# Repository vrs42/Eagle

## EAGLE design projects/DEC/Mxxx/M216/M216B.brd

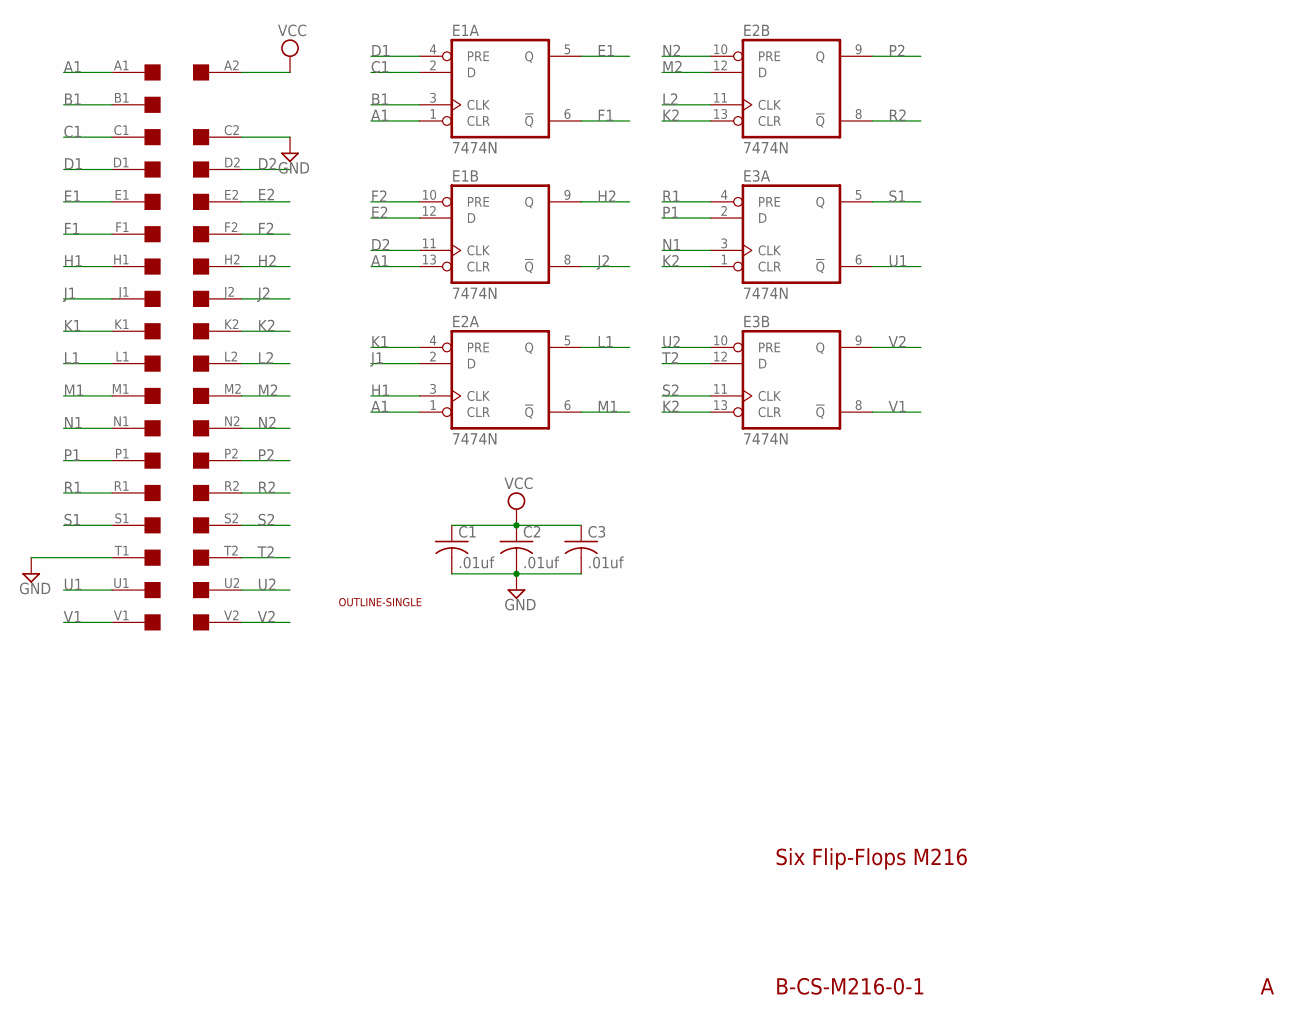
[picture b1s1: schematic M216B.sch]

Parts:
C1, C2, C3: .01uf; C050-025X075
E1, E2, E3: 7474N; DIL14
U$1: OUTLINE-SINGLE; SINGLE
U$4: SINGLE; EDGE-CON2

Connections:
A1: E1.1 (CLR), E1.13 (CLR), E2.1 (CLR), U$4.A1
B1: E1.3 (CLK), U$4.B1
C1: E1.2 (D), U$4.C1
D1: E1.4 (PRE), U$4.D1
D2: E1.11 (CLK), U$4.D2
E1: E1.5 (Q), U$4.E1
E2: E1.12 (D), U$4.E2
F1: E1.6 (!Q), U$4.F1
F2: E1.10 (PRE), U$4.F2
GND: C1.2, C2.2, C3.2, E1.7 (GND), E2.7 (GND), E3.7 (GND), U$4.C2, U$4.T1
H1: E2.3 (CLK), U$4.H1
H2: E1.9 (Q), U$4.H2
J1: E2.2 (D), U$4.J1
J2: E1.8 (!Q), U$4.J2
K1: E2.4 (PRE), U$4.K1
K2: E2.13 (CLR), E3.1 (CLR), E3.13 (CLR), U$4.K2
L1: E2.5 (Q), U$4.L1
L2: E2.11 (CLK), U$4.L2
M1: E2.6 (!Q), U$4.M1
M2: E2.12 (D), U$4.M2
N1: E3.3 (CLK), U$4.N1
N2: E2.10 (PRE), U$4.N2
P1: E3.2 (D), U$4.P1
P2: E2.9 (Q), U$4.P2
R1: E3.4 (PRE), U$4.R1
R2: E2.8 (!Q), U$4.R2
S1: E3.5 (Q), U$4.S1
S2: E3.11 (CLK), U$4.S2
T2: E3.12 (D), U$4.T2
U1: E3.6 (!Q), U$4.U1
U2: E3.10 (PRE), U$4.U2
V1: E3.8 (!Q), U$4.V1
V2: E3.9 (Q), U$4.V2
VCC: C1.1, C2.1, C3.1, E1.14 (VCC), E2.14 (VCC), E3.14 (VCC), U$4.A2

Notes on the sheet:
B-CS-M216-0-1
Six Flip-Flops M216

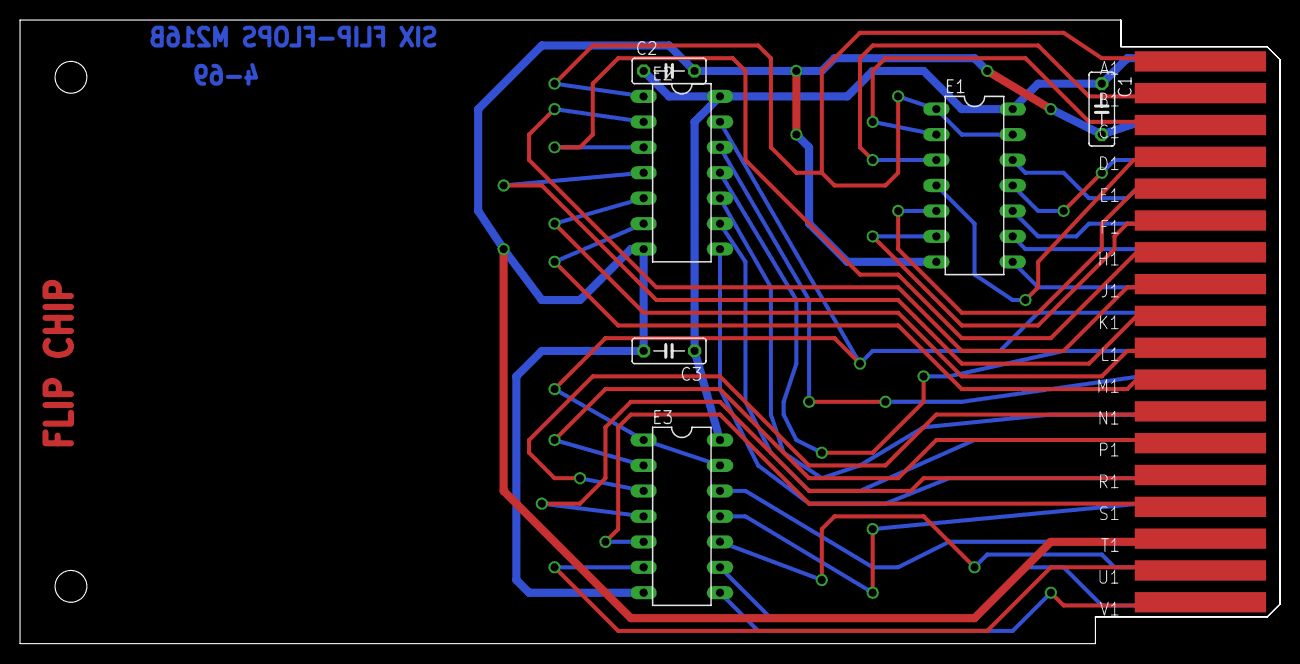
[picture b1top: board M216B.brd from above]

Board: 2 copper layers, 125.7 x 62.2 mm, 9 parts (0 on the bottom side), 34 nets.

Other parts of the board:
U$5: FLIPCHIP

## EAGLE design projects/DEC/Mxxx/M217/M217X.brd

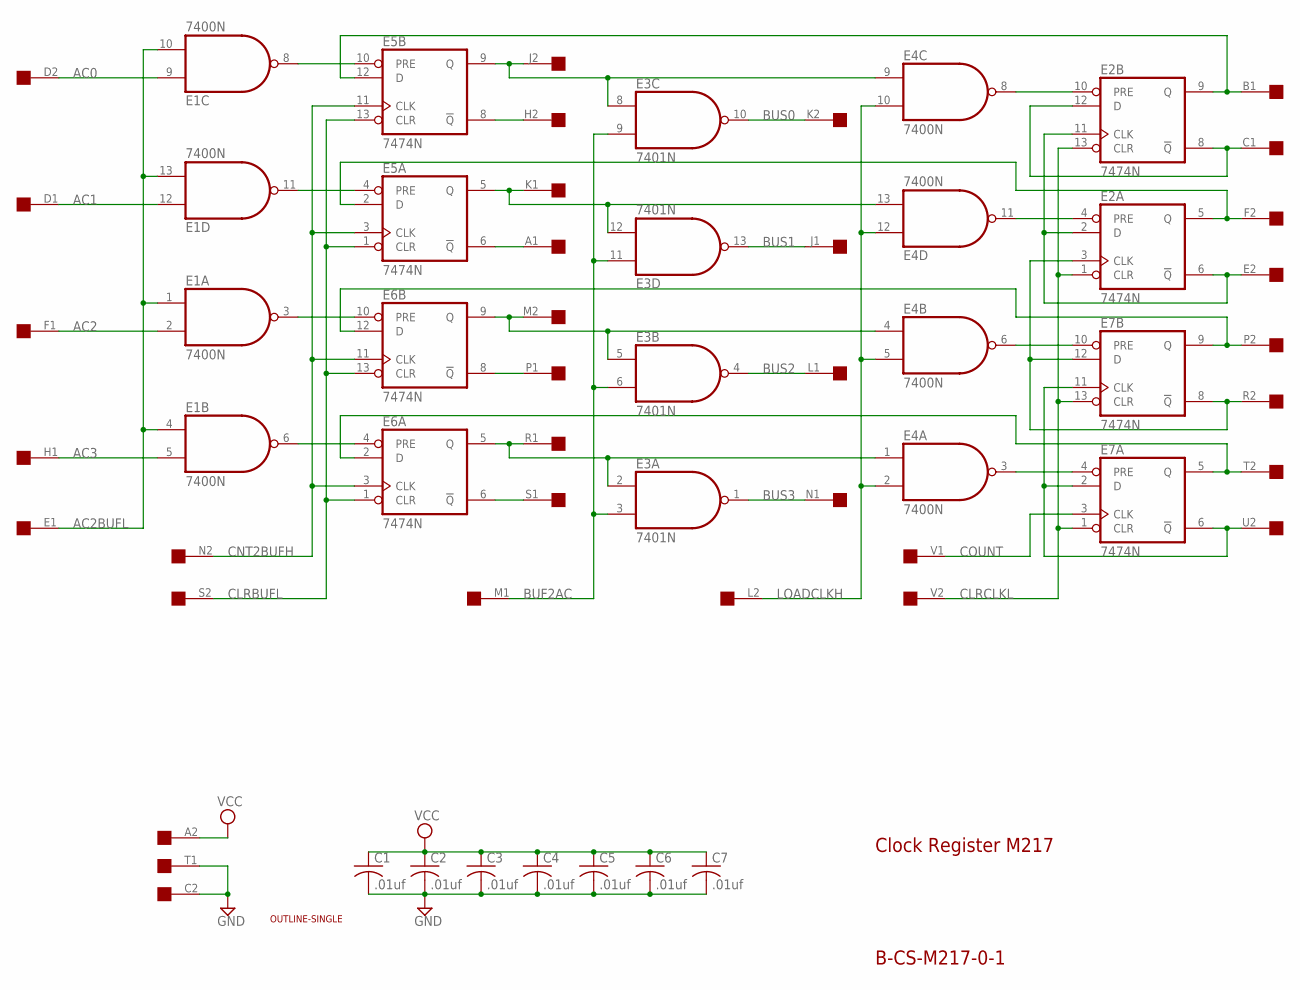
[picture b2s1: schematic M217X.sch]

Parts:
C1, C2, C3, C4, C5, C6, C7: .01uf; C050-025X075
E1, E4: 7400N; DIL14
E2, E5, E6, E7: 7474N; DIL14
E3: 7401N; DIL14
U$1: OUTLINE-SINGLE; SINGLE
U$4: SINGLE; EDGE-CON2

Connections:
AC0: E1.9 (I0), U$4.D2
AC1: E1.12 (I0), U$4.D1
AC2: E1.2 (I1), U$4.F1
AC2BUFL: E1.1 (I0), E1.4 (I0), E1.10 (I1), E1.13 (I1), U$4.E1
AC3: E1.5 (I1), U$4.H1
BUF2AC: E3.3 (I1), E3.6 (I1), E3.9 (I1), E3.11 (I0), U$4.M1
BUS0: E3.10 (O), U$4.K2
BUS1: E3.13 (O), U$4.J1
BUS2: E3.4 (O), U$4.L1
BUS3: E3.1 (O), U$4.N1
CLRBUFL: E5.1 (CLR), E5.13 (CLR), E6.1 (CLR), E6.13 (CLR), U$4.S2
CLRCLKL: E2.1 (CLR), E2.13 (CLR), E7.1 (CLR), E7.13 (CLR), U$4.V2
CNT2BUFH: E5.3 (CLK), E5.11 (CLK), E6.3 (CLK), E6.11 (CLK), U$4.N2
COUNT: E7.3 (CLK), U$4.V1
GND: C1.2, C2.2, C3.2, C4.2, C5.2, C6.2, C7.2, E1.7 (GND), E2.7 (GND), E3.7 (GND), E4.7 (GND), E5.7 (GND), E6.7 (GND), E7.7 (GND), U$4.C2, U$4.T1
LOADCLKH: E4.2 (I1), E4.5 (I1), E4.10 (I1), E4.12 (I0), U$4.L2
unnamed: E6.12 (D), E7.9 (Q), U$4.P2
unnamed: E2.5 (Q), E5.2 (D), U$4.F2
unnamed: E1.6 (O), E6.4 (PRE)
unnamed: E1.3 (O), E6.10 (PRE)
unnamed: E1.11 (O), E5.4 (PRE)
unnamed: E1.8 (O), E5.10 (PRE)
unnamed: E3.8 (I0), E4.9 (I0), E5.9 (Q), U$4.J2
unnamed: E5.8 (!Q), U$4.H2
unnamed: E3.12 (I1), E4.13 (I1), E5.5 (Q), U$4.K1
unnamed: E5.6 (!Q), U$4.A1
unnamed: E3.5 (I0), E4.4 (I0), E6.9 (Q), U$4.M2
unnamed: E6.8 (!Q), U$4.P1
unnamed: E3.2 (I0), E4.1 (I0), E6.5 (Q), U$4.R1
unnamed: E6.6 (!Q), U$4.S1
unnamed: E4.3 (O), E7.4 (PRE)
unnamed: E4.6 (O), E7.10 (PRE)
unnamed: E2.4 (PRE), E4.11 (O)
unnamed: E2.10 (PRE), E4.8 (O)
unnamed: E7.2 (D), E7.6 (!Q), E7.11 (CLK), U$4.U2
unnamed: E6.2 (D), E7.5 (Q), U$4.T2
unnamed: E2.3 (CLK), E7.8 (!Q), E7.12 (D), U$4.R2
unnamed: E2.2 (D), E2.6 (!Q), E2.11 (CLK), U$4.E2
unnamed: E2.9 (Q), E5.12 (D), U$4.B1
unnamed: E2.8 (!Q), E2.12 (D), U$4.C1
VCC: C1.1, C2.1, C3.1, C4.1, C5.1, C6.1, C7.1, E1.14 (VCC), E2.14 (VCC), E3.14 (VCC), E4.14 (VCC), E5.14 (VCC), E6.14 (VCC), E7.14 (VCC), U$4.A2

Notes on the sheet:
B-CS-M217-0-1
Clock Register M217

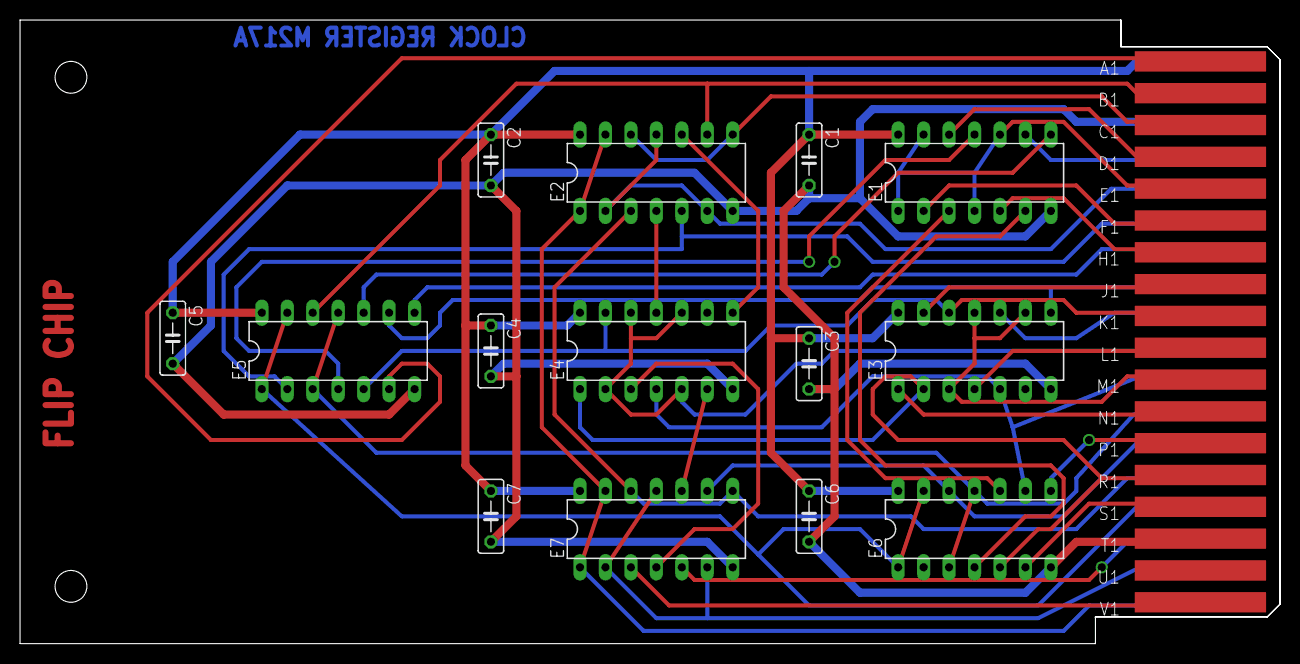
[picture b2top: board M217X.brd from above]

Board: 2 copper layers, 125.7 x 62.2 mm, 17 parts (0 on the bottom side), 41 nets.

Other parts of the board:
U$5: FLIPCHIP

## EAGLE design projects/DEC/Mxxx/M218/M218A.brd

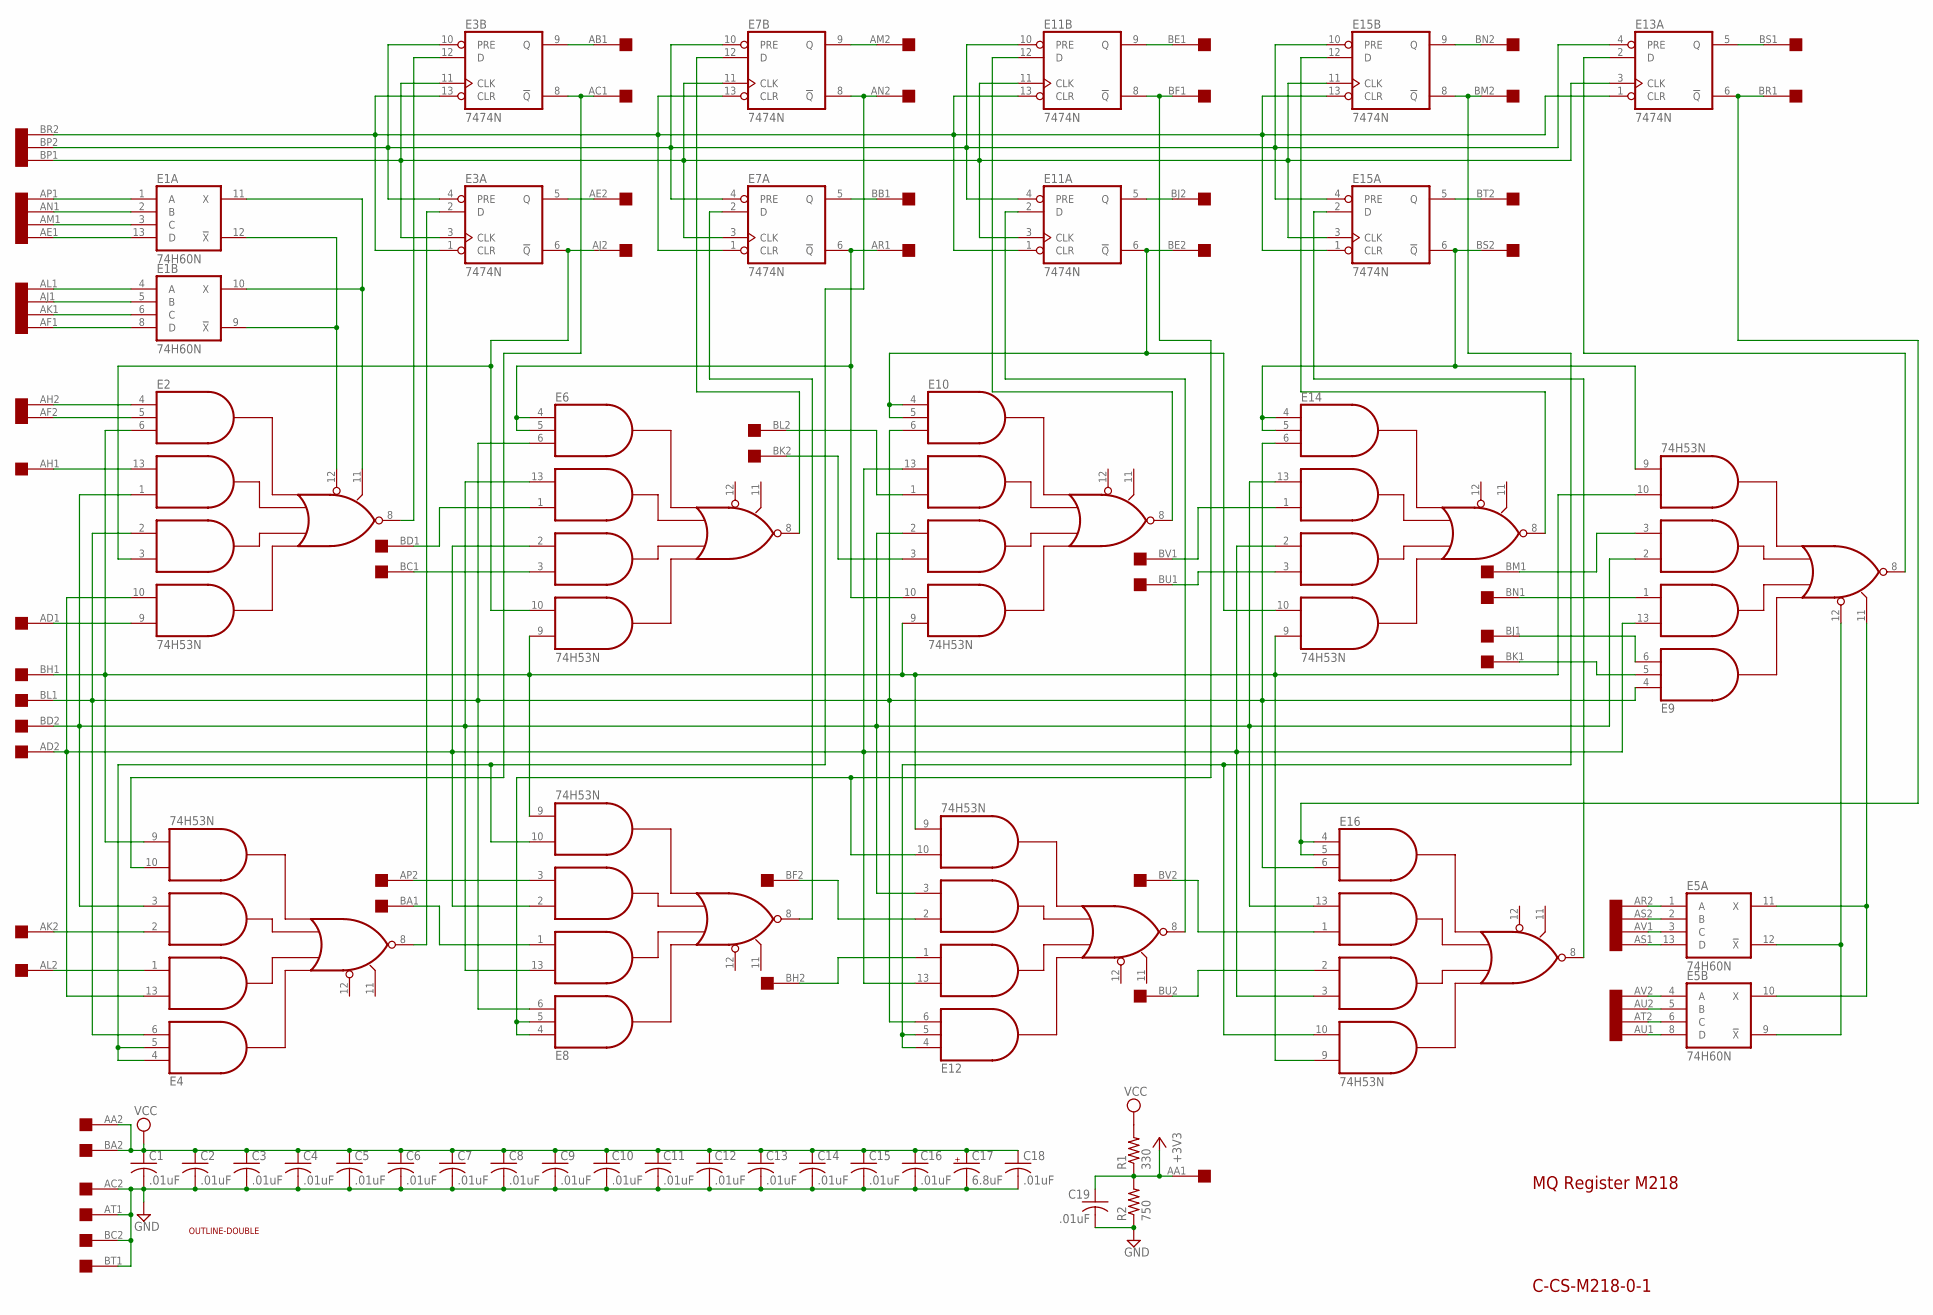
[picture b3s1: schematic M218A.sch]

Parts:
C1, C2, C3, C4, C5, C6, C7, C8, C9, C10, C11, C12, C13, C14, C15, C16, C18, C19: .01uF; C050-025X075
C17: 6.8uF; E12-8
E1, E5: 74H60N; DIL14
E2, E4, E6, E8, E9, E10, E12, E14, E16: 74H53N; DIL14
E3, E7, E11, E13, E15: 7474N; DIL14
R1: 330; 0207/10
R2: 750; 0207/10
U$1: OUTLINE-DOUBLE; DOUBLE
U$3: DOUBLE; EDGE-CON4

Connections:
+3V3: C19.1, R1.1, R2.2, U$3.AA1
GND: C1.2, C2.2, C3.2, C4.2, C5.2, C6.2, C7.2, C8.2, C9.2, C10.2, C11.2, C12.2, C13.2, C14.2, C15.2, C16.2, C17.-, C18.2, C19.2, E1.7 (GND), E2.7 (GND), E3.7 (GND), E4.7 (GND), E5.7 (GND), E6.7 (GND), E7.7 (GND), E8.7 (GND), E9.7 (GND), E10.7 (GND), E11.7 (GND), E12.7 (GND), E13.7 (GND), E14.7 (GND), E15.7 (GND), E16.7 (GND), R2.1, U$3.AC2, U$3.AT1, U$3.BC2, U$3.BT1
unnamed: E1.9 (!X), E1.12 (!X), E2.12 (I9)
unnamed: E1.10 (X), E1.11 (X), E2.11 (I10)
unnamed: E1.1 (A), U$3.AP1
unnamed: E1.3 (C), U$3.AM1
unnamed: E1.2 (B), U$3.AN1
unnamed: E1.13 (D), U$3.AE1
unnamed: E1.4 (A), U$3.AL1
unnamed: E1.5 (B), U$3.AJ1
unnamed: E1.6 (C), U$3.AK1
unnamed: E1.8 (D), U$3.AF1
unnamed: E2.4 (I1), U$3.AH2
unnamed: E2.5 (I11), U$3.AF2
unnamed: E2.6 (I2), E4.9 (I8), E6.9 (I8), E8.9 (I8), E9.10 (I7), E10.9 (I8), E12.9 (I8), E14.9 (I8), E16.9 (I8), U$3.BH1
unnamed: E2.13 (I3), U$3.AH1
unnamed: E2.1 (I4), E4.3 (I6), E6.13 (I3), E8.13 (I3), E9.2 (I5), E10.2 (I5), E12.3 (I6), E14.13 (I3), E16.13 (I3), U$3.BD2
unnamed: E2.2 (I5), E4.6 (I2), E6.6 (I2), E8.6 (I2), E9.4 (I1), E10.6 (I2), E12.6 (I2), E14.6 (I2), E16.6 (I2), U$3.BL1
unnamed: E2.3 (I6), E3.6 (!Q), E6.10 (I7), U$3.AJ2
unnamed: E2.9 (I8), U$3.AD1
unnamed: E2.10 (I7), E4.13 (I3), E6.2 (I5), E8.2 (I5), E9.13 (I3), E10.13 (I3), E12.13 (I3), E14.2 (I5), E16.3 (I6), U$3.AD2
unnamed: E3.8 (!Q), E4.10 (I7), U$3.AC1
unnamed: E4.1 (I4), U$3.AL2
unnamed: E4.2 (I5), U$3.AK2
unnamed: E4.4 (I1), E4.5 (I11), E7.8 (!Q), E8.10 (I7), U$3.AN2
unnamed: E3.1 (CLR), E3.13 (CLR), E7.1 (CLR), E7.13 (CLR), E11.1 (CLR), E11.13 (CLR), E13.1 (CLR), E15.1 (CLR), E15.13 (CLR), U$3.BR2
unnamed: E3.2 (D), E4.8 (O)
unnamed: E3.4 (PRE), E3.10 (PRE), E7.4 (PRE), E7.10 (PRE), E11.4 (PRE), E11.10 (PRE), E13.4 (PRE), E15.4 (PRE), E15.10 (PRE), U$3.BP2
unnamed: E3.3 (CLK), E3.11 (CLK), E7.3 (CLK), E7.11 (CLK), E11.3 (CLK), E11.11 (CLK), E13.3 (CLK), E15.3 (CLK), E15.11 (CLK), U$3.BP1
unnamed: E2.8 (O), E3.12 (D)
unnamed: E8.3 (I6), U$3.AP2
unnamed: E3.9 (Q), U$3.AB1
unnamed: E3.5 (Q), U$3.AE2
unnamed: E6.4 (I1), E6.5 (I11), E7.6 (!Q), E10.10 (I7), U$3.AR1
unnamed: E6.3 (I6), U$3.BC1
unnamed: E6.1 (I4), U$3.BD1
unnamed: E8.4 (I1), E8.5 (I11), E11.8 (!Q), E12.10 (I7), U$3.BF1
unnamed: E8.1 (I4), U$3.BA1
unnamed: E6.8 (O), E7.12 (D)
unnamed: E7.2 (D), E8.8 (O)
unnamed: E10.4 (I1), E10.5 (I11), E11.6 (!Q), E14.10 (I7), U$3.BE2
unnamed: E7.9 (Q), U$3.AM2
unnamed: E7.5 (Q), U$3.BB1
unnamed: E9.8 (O), E13.2 (D)
unnamed: E9.9 (I8), E14.4 (I1), E14.5 (I11), E15.6 (!Q), U$3.BS2
unnamed: E11.9 (Q), U$3.BE1
unnamed: E11.5 (Q), U$3.BJ2
unnamed: E12.4 (I1), E12.5 (I11), E15.8 (!Q), E16.10 (I7), U$3.BM2
unnamed: E15.9 (Q), U$3.BN2
unnamed: E15.5 (Q), U$3.BT2
unnamed: E13.6 (!Q), E16.4 (I1), E16.5 (I11), U$3.BR1
unnamed: E13.5 (Q), U$3.BS1
unnamed: E5.1 (A), U$3.AR2
unnamed: E5.2 (B), U$3.AS2
unnamed: E5.3 (C), U$3.AV1
unnamed: E5.13 (D), U$3.AS1
unnamed: E5.4 (A), U$3.AV2
unnamed: E5.5 (B), U$3.AU2
unnamed: E5.6 (C), U$3.AT2
unnamed: E5.8 (D), U$3.AU1
unnamed: E5.10 (X), E5.11 (X), E9.11 (I10)
unnamed: E5.9 (!X), E5.12 (!X), E9.12 (I9)
unnamed: E10.8 (O), E11.12 (D)
unnamed: E11.2 (D), E12.8 (O)
unnamed: E10.1 (I4), U$3.BL2
unnamed: E10.3 (I6), U$3.BK2
unnamed: E12.1 (I4), U$3.BH2
unnamed: E12.2 (I5), U$3.BF2
unnamed: E9.6 (I2), U$3.BJ1
unnamed: E14.8 (O), E15.12 (D)
unnamed: E15.2 (D), E16.8 (O)
unnamed: E14.3 (I6), U$3.BU1
unnamed: E14.1 (I4), U$3.BV1
unnamed: E16.1 (I4), U$3.BV2
unnamed: E16.2 (I5), U$3.BU2
unnamed: E9.5 (I11), U$3.BK1
unnamed: E9.3 (I6), U$3.BM1
unnamed: E9.1 (I4), U$3.BN1
VCC: C1.1, C2.1, C3.1, C4.1, C5.1, C6.1, C7.1, C8.1, C9.1, C10.1, C11.1, C12.1, C13.1, C14.1, C15.1, C16.1, C17.+, C18.1, E1.14 (VCC), E2.14 (VCC), E3.14 (VCC), E4.14 (VCC), E5.14 (VCC), E6.14 (VCC), E7.14 (VCC), E8.14 (VCC), E9.14 (VCC), E10.14 (VCC), E11.14 (VCC), E12.14 (VCC), E13.14 (VCC), E14.14 (VCC), E15.14 (VCC), E16.14 (VCC), R1.2, U$3.AA2, U$3.BA2

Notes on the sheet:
MQ Register M218
C-CS-M218-0-1

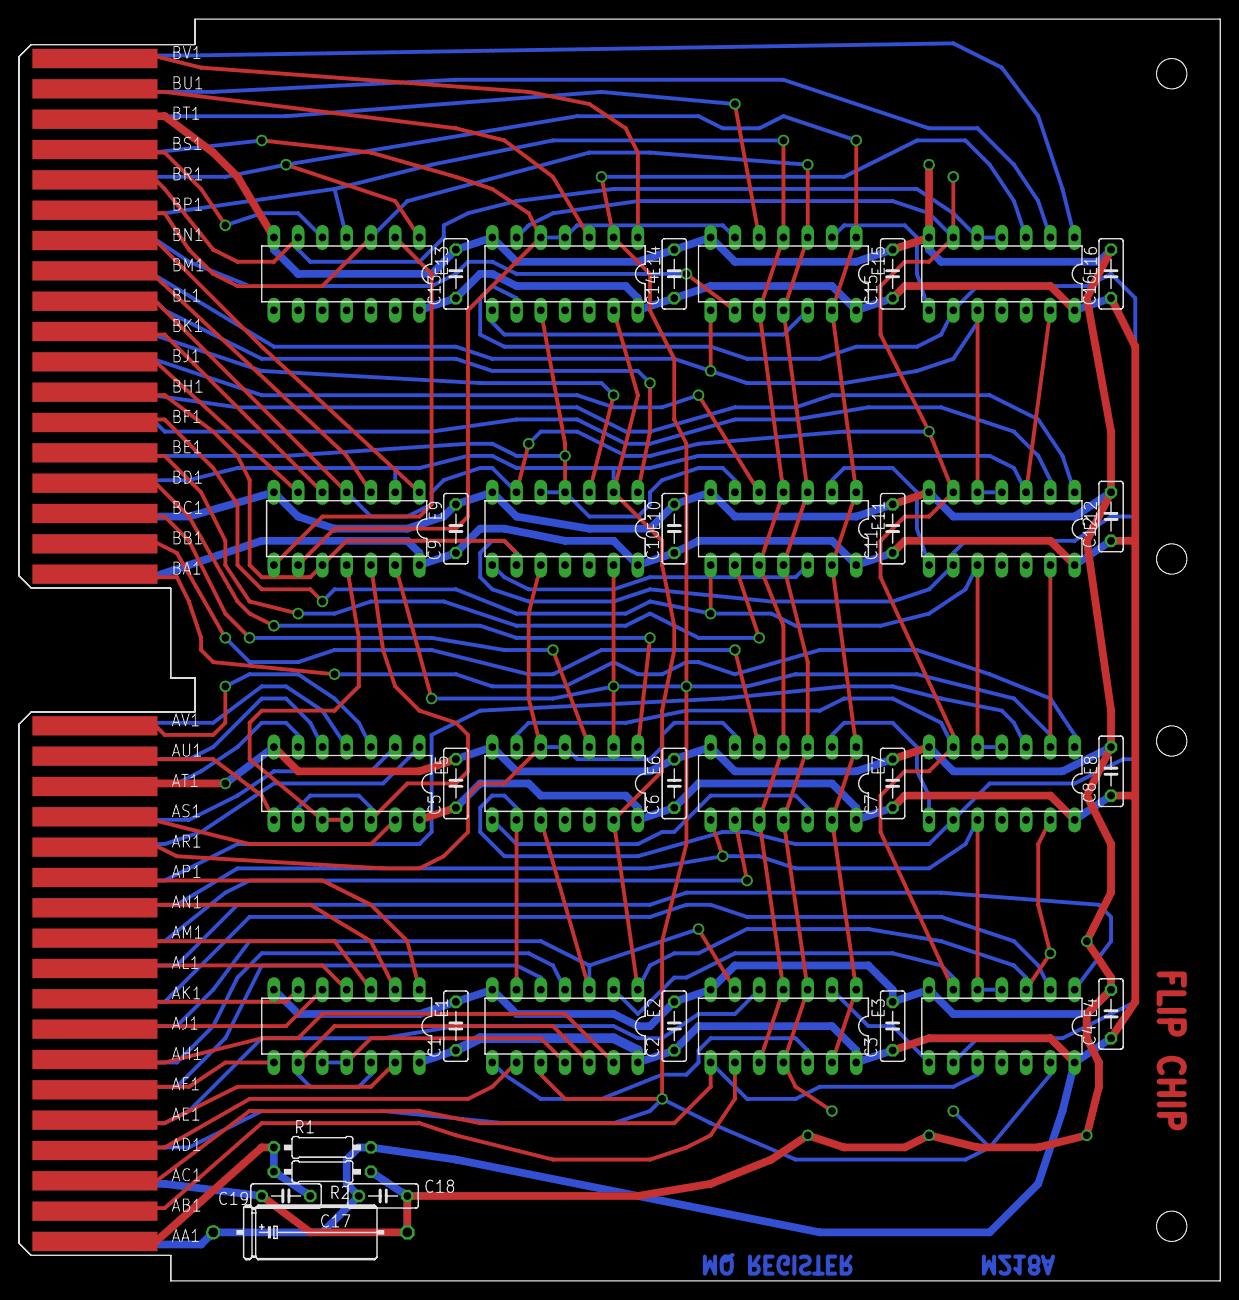
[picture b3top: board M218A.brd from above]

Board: 2 copper layers, 125.7 x 132.1 mm, 39 parts (0 on the bottom side), 79 nets.

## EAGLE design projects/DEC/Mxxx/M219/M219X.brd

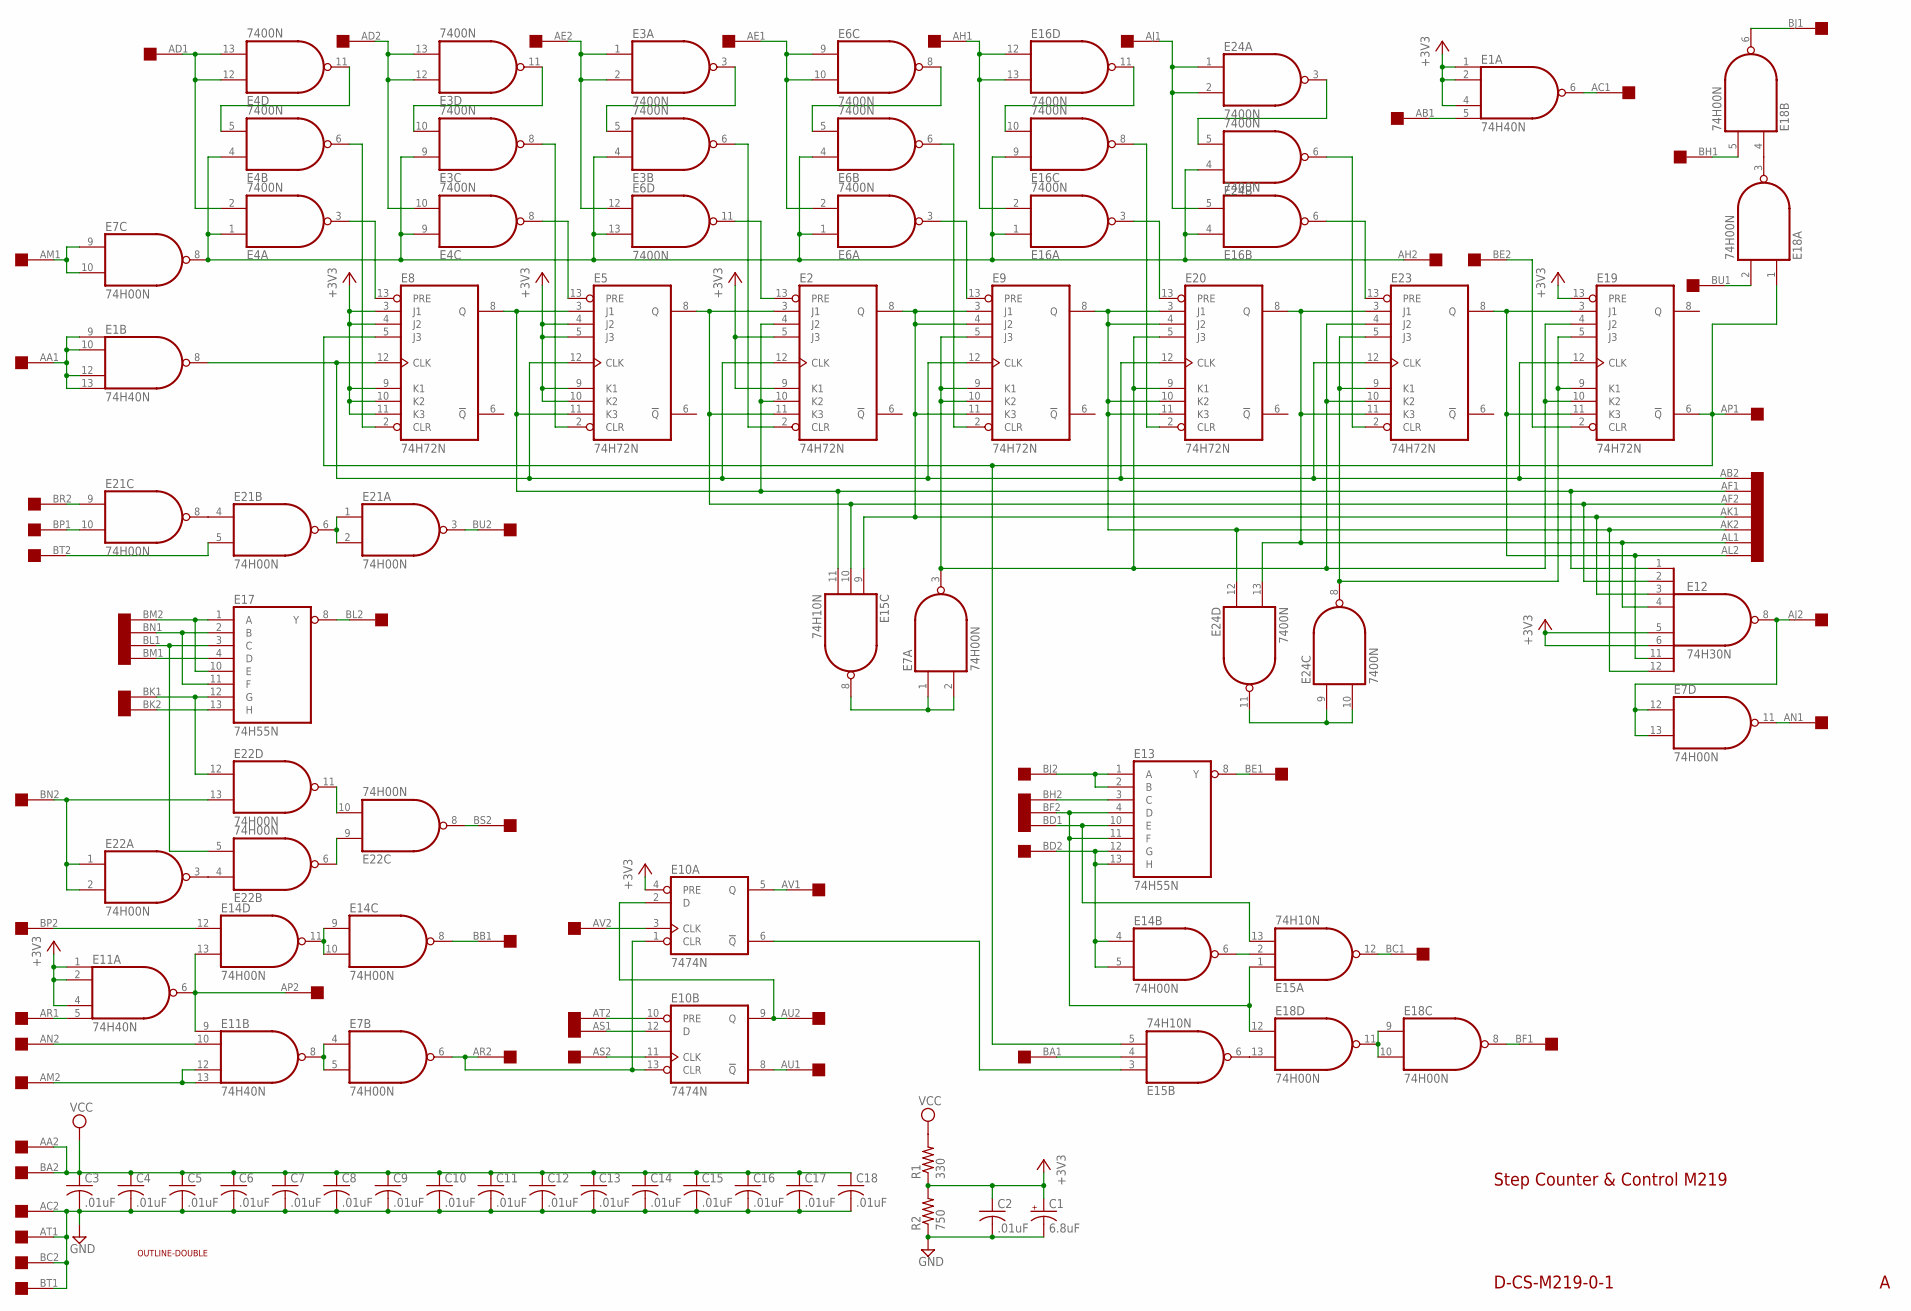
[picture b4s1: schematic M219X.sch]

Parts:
C1: 6.8uF; E12-8
C2, C3, C4, C5, C6, C7, C8, C9, C10, C11, C12, C13, C14, C15, C16, C17, C18: .01uF; C050-025X075
E1, E11: 74H40N; DIL14
E2, E5, E8, E9, E19, E20, E23: 74H72N; DIL14
E3, E4, E6, E16, E24: 7400N; DIL14
E7, E14, E18, E21, E22: 74H00N; DIL14
E10: 7474N; DIL14
E12: 74H30N; DIL14
E13, E17: 74H55N; DIL14
E15: 74H10N; DIL14
R1: 330; 0207/10
R2: 750; 0207/10
U$1: OUTLINE-DOUBLE; DOUBLE
U$3: DOUBLE; EDGE-CON4

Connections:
+3V3: C1.+, C2.1, E1.1 (I0), E1.2 (I1), E1.4 (I2), E2.5 (J3), E2.9 (K1), E5.4 (J2), E5.5 (J3), E5.9 (K1), E5.10 (K2), E8.3 (J1), E8.4 (J2), E8.9 (K1), E8.10 (K2), E8.11 (K3), E10.4 (PRE), E11.1 (I0), E11.2 (I1), E11.4 (I2), E12.5 (I4), E12.6 (I5), E19.13 (PRE), R1.1, R2.2
GND: C1.-, C2.2, C3.2, C4.2, C5.2, C6.2, C7.2, C8.2, C9.2, C10.2, C11.2, C12.2, C13.2, C14.2, C15.2, C16.2, C17.2, C18.2, E1.7 (GND), E2.7 (GND), E3.7 (GND), E4.7 (GND), E5.7 (GND), E6.7 (GND), E7.7 (GND), E8.7 (GND), E9.7 (GND), E10.7 (GND), E11.7 (GND), E12.7 (GND), E13.7 (GND), E14.7 (GND), E15.7 (GND), E16.7 (GND), E17.7 (GND), E18.7 (GND), E19.7 (GND), E20.7 (GND), E21.7 (GND), E22.7 (GND), E23.7 (GND), E24.7 (GND), R2.1, U$3.AC2, U$3.AT1, U$3.BC2, U$3.BT1
unnamed: E1.9 (I0), E1.10 (I1), E1.12 (I2), E1.13 (I3), U$3.AA1
unnamed: E1.8 (O), E2.12 (CLK), E5.12 (CLK), E8.12 (CLK), E9.12 (CLK), E19.12 (CLK), E20.12 (CLK), E23.12 (CLK), U$3.AB2
unnamed: E4.2 (I1), E4.12 (I0), E4.13 (I1), U$3.AD1
unnamed: E7.9 (I0), E7.10 (I1), U$3.AM1
unnamed: E8.5 (J3), E15.5 (I2), E18.1 (I0), E19.6 (!Q), U$3.AP1
unnamed: E3.4 (I0), E3.9 (I0), E4.1 (I0), E4.4 (I0), E4.9 (I0), E6.1 (I0), E6.4 (I0), E6.13 (I1), E7.8 (O), E16.1 (I0), E16.4 (I0), E16.9 (I0), E24.4 (I0), U$3.AH2
unnamed: E4.5 (I1), E4.11 (O)
unnamed: E4.3 (O), E8.13 (PRE)
unnamed: E4.8 (O), E5.13 (PRE)
unnamed: E3.12 (I0), E3.13 (I1), E4.10 (I1), U$3.AD2
unnamed: E6.3 (O), E9.13 (PRE)
unnamed: E6.2 (I1), E6.9 (I0), E6.10 (I1), U$3.AE1
unnamed: E3.1 (I0), E3.2 (I1), E6.12 (I0), U$3.AE2
unnamed: E2.13 (PRE), E6.11 (O)
unnamed: E16.3 (O), E20.13 (PRE)
unnamed: E16.6 (O), E23.13 (PRE)
unnamed: E4.6 (O), E8.2 (CLR)
unnamed: E3.8 (O), E5.2 (CLR)
unnamed: E3.10 (I1), E3.11 (O)
unnamed: E2.4 (J2), E2.10 (K2), E5.3 (J1), E5.11 (K3), E8.8 (Q), E12.1 (I0), E15.11 (I2), U$3.AF1
unnamed: E2.3 (J1), E2.11 (K3), E5.8 (Q), E12.2 (I1), E15.10 (I1), U$3.AF2
unnamed: E2.8 (Q), E9.3 (J1), E9.4 (J2), E9.11 (K3), E12.3 (I2), E15.9 (I0), U$3.AK1
unnamed: E9.8 (Q), E12.12 (I7), E20.3 (J1), E20.4 (J2), E20.10 (K2), E20.11 (K3), E24.12 (I0), U$3.AK2
unnamed: E12.4 (I3), E20.8 (Q), E23.3 (J1), E23.11 (K3), E24.13 (I1), U$3.AL1
unnamed: E12.11 (I6), E19.3 (J1), E19.11 (K3), E23.8 (Q), U$3.AL2
unnamed: E2.2 (CLR), E3.6 (O)
unnamed: E3.3 (O), E3.5 (I1)
unnamed: E6.5 (I1), E6.8 (O)
unnamed: E6.6 (O), E9.2 (CLR)
unnamed: E7.3 (O), E9.5 (J3), E9.9 (K1), E9.10 (K2), E19.4 (J2), E19.10 (K2), E20.5 (J3), E20.9 (K1), E23.4 (J2), E23.10 (K2)
unnamed: E7.1 (I0), E7.2 (I1), E15.8 (O)
unnamed: E16.10 (I1), E16.11 (O)
unnamed: E16.2 (I1), E16.12 (I0), E16.13 (I1), U$3.AH1
unnamed: E16.8 (O), E20.2 (CLR)
unnamed: E24.3 (O), E24.5 (I1)
unnamed: E16.5 (I1), E24.1 (I0), E24.2 (I1), U$3.AJ1
unnamed: E23.2 (CLR), E24.6 (O)
unnamed: E19.5 (J3), E19.9 (K1), E23.5 (J3), E23.9 (K1), E24.8 (O)
unnamed: E1.5 (I3), U$3.AB1
unnamed: E24.9 (I0), E24.10 (I1), E24.11 (O)
unnamed: E1.6 (O), U$3.AC1
unnamed: E7.12 (I0), E7.13 (I1), E12.8 (O), U$3.AJ2
unnamed: E7.11 (O), U$3.AN1
unnamed: E17.3 (C), E22.5 (I1), U$3.BL1
unnamed: E18.3 (O), E18.4 (I0)
unnamed: E18.2 (I1), U$3.BU1
unnamed: E18.5 (I1), U$3.BH1
unnamed: E18.6 (O), U$3.BJ1
unnamed: E21.4 (I0), E21.8 (O)
unnamed: E21.9 (I0), U$3.BR2
unnamed: E21.10 (I1), U$3.BP1
unnamed: E21.5 (I1), U$3.BT2
unnamed: E21.1 (I0), E21.2 (I1), E21.6 (O)
unnamed: E21.3 (O), U$3.BU2
unnamed: E22.6 (O), E22.9 (I0)
unnamed: E22.10 (I1), E22.11 (O)
unnamed: E22.3 (O), E22.4 (I0)
unnamed: E22.1 (I0), E22.2 (I1), E22.13 (I1), U$3.BN2
unnamed: E17.12 (G), E22.12 (I0), U$3.BK1
unnamed: E17.4 (D), U$3.BM1
unnamed: E17.1 (A), E17.10 (E), U$3.BM2
unnamed: E17.2 (B), E17.11 (F), U$3.BN1
unnamed: E17.13 (H), U$3.BK2
unnamed: E17.8 (Y), U$3.BL2
unnamed: E22.8 (O), U$3.BS2
unnamed: E11.5 (I3), U$3.AR1
unnamed: E11.6 (O), E11.9 (I0), E14.13 (I1), U$3.AP2
unnamed: E11.12 (I2), E11.13 (I3), U$3.AM2
unnamed: E11.10 (I1), U$3.AN2
unnamed: E14.12 (I0), U$3.BP2
unnamed: E14.9 (I0), E14.10 (I1), E14.11 (O)
unnamed: E7.4 (I0), E7.5 (I1), E11.8 (O)
unnamed: E14.8 (O), U$3.BB1
unnamed: E7.6 (O), E10.1 (CLR), E10.13 (CLR), U$3.AR2
unnamed: E10.11 (CLK), U$3.AS2
unnamed: E10.12 (D), U$3.AS1
unnamed: E10.10 (PRE), U$3.AT2
unnamed: E10.2 (D), E10.9 (Q), U$3.AU2
unnamed: E10.3 (CLK), U$3.AV2
unnamed: E10.5 (Q), U$3.AV1
unnamed: E10.8 (!Q), U$3.AU1
unnamed: E13.1 (A), E13.2 (B), U$3.BJ2
unnamed: E13.3 (C), U$3.BH2
unnamed: E13.4 (D), E13.11 (F), E15.1 (I0), E18.12 (I0), U$3.BF2
unnamed: E13.10 (E), E15.13 (I2), U$3.BD1
unnamed: E13.12 (G), E13.13 (H), E14.4 (I0), E14.5 (I1), U$3.BD2
unnamed: E14.6 (O), E15.2 (I1)
unnamed: E13.8 (Y), U$3.BE1
unnamed: E15.12 (O), U$3.BC1
unnamed: E15.4 (I1), U$3.BA1
unnamed: E15.6 (O), E18.13 (I1)
unnamed: E10.6 (!Q), E15.3 (I0)
unnamed: E18.9 (I0), E18.10 (I1), E18.11 (O)
unnamed: E18.8 (O), U$3.BF1
unnamed: E19.2 (CLR), U$3.BE2
VCC: C3.1, C4.1, C5.1, C6.1, C7.1, C8.1, C9.1, C10.1, C11.1, C12.1, C13.1, C14.1, C15.1, C16.1, C17.1, C18.1, E1.14 (VCC), E2.14 (VCC), E3.14 (VCC), E4.14 (VCC), E5.14 (VCC), E6.14 (VCC), E7.14 (VCC), E8.14 (VCC), E9.14 (VCC), E10.14 (VCC), E11.14 (VCC), E12.14 (VCC), E13.14 (VCC), E14.14 (VCC), E15.14 (VCC), E16.14 (VCC), E17.14 (VCC), E18.14 (VCC), E19.14 (VCC), E20.14 (VCC), E21.14 (VCC), E22.14 (VCC), E23.14 (VCC), E24.14 (VCC), R1.2, U$3.AA2, U$3.BA2

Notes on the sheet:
Step Counter & Control M219
D-CS-M219-0-1

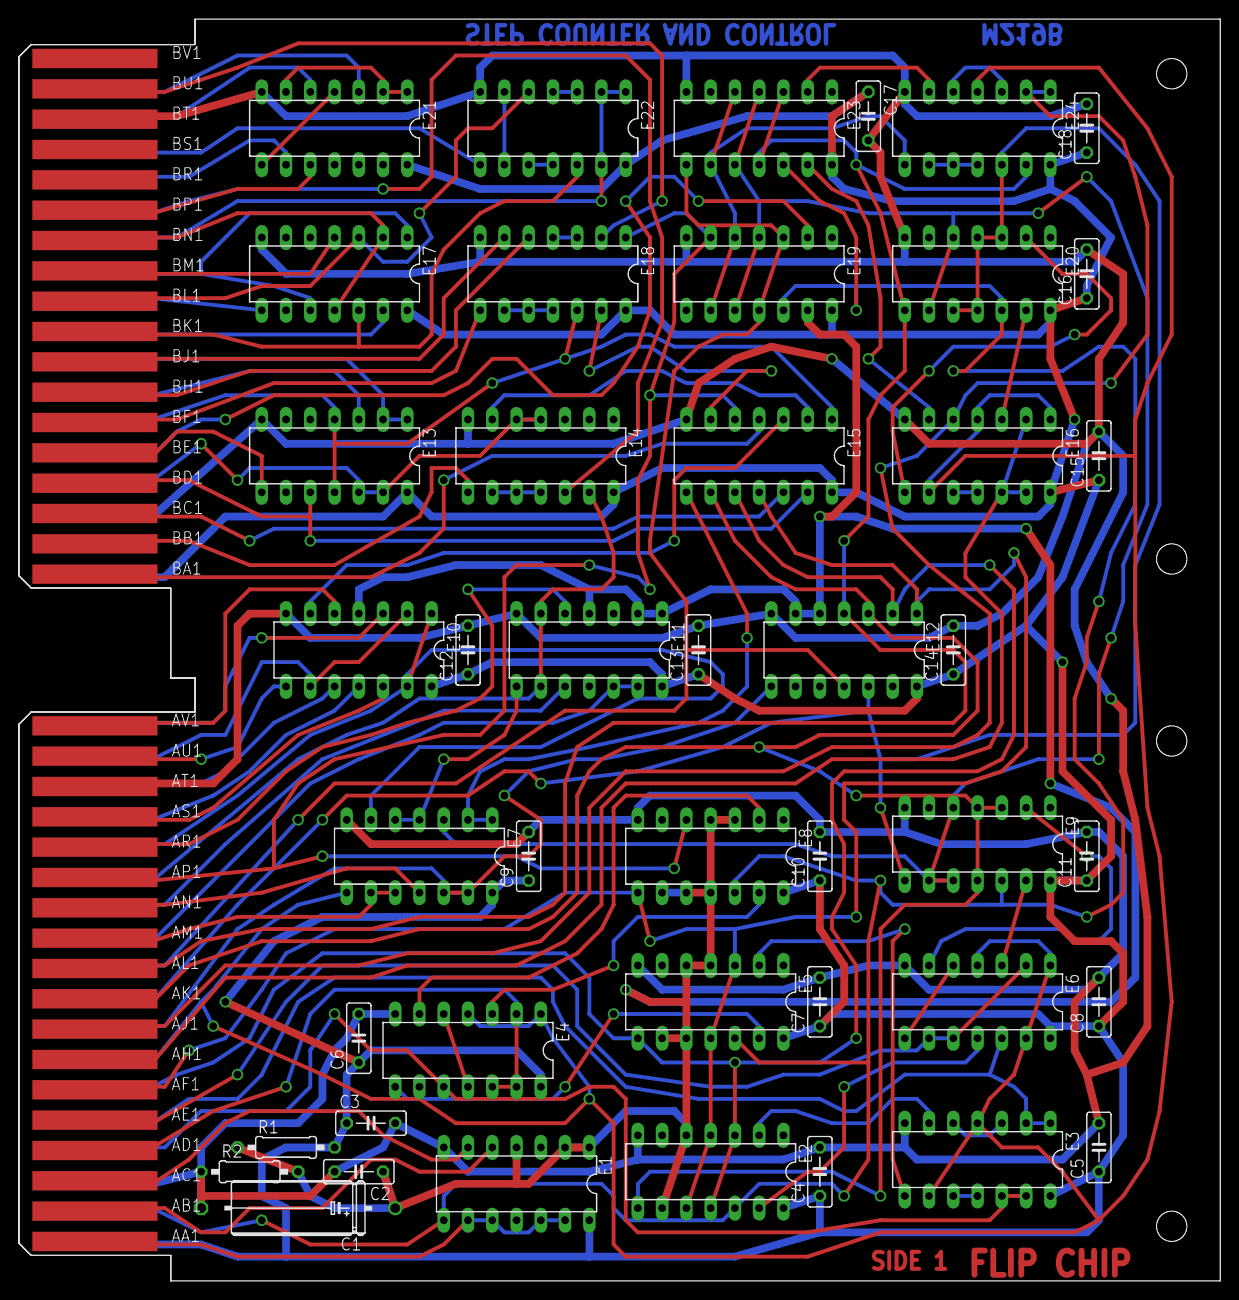
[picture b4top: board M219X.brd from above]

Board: 2 copper layers, 125.7 x 132.1 mm, 46 parts (0 on the bottom side), 98 nets.
